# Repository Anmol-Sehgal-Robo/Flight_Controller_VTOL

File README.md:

# VTOL R2 Flight Controller

A single-string flight controller board for a 1.6 m tilt-rotor tricopter VTOL, designed in KiCad 9 and intended to run ArduPilot.

> **Status: design stage, not yet fabricated or bench-tested.** Items marked "simulated" or "assumed" have not been verified on hardware. Do not treat this design as flight-proven.

## Overview

- **Vehicle:** Heewing T1-style tilt-rotor tricopter, 1.6 m span, ~30 min flight time target
- **Firmware target:** ArduPilot
- **Architecture:** single-string (no redundancy)
- **Battery:** 6S Li-ion (6S2P 21700)

## Board

| Item | Value |
|---|---|
| MCU | STM32H743 |
| IMU | BMI270 |
| Barometer | BMP581 |
| Power stage | LT8641 buck, 2 MHz, 5 V rail |
| Size / layers | 70 x 55 mm, 4-layer |
| Servo outputs | 12 x 3-pin headers |
| Other | microSD, USB, SWD, buzzer |
| Fabrication | JLCPCB |

## Current state

- Layout: 0 unrouted nets, 0 DRC errors
- BOM checked against LCSC/JLC part pages
- Power stage simulated in LTspice and ngspice (efficiency figures indicative only, some derating values assumed)
- Not yet fabricated

## Safety

Unvalidated prototype. Do not fly until the board has passed bring-up and bench testing, and always power up first from a current-limited supply.

## License

To be decided.

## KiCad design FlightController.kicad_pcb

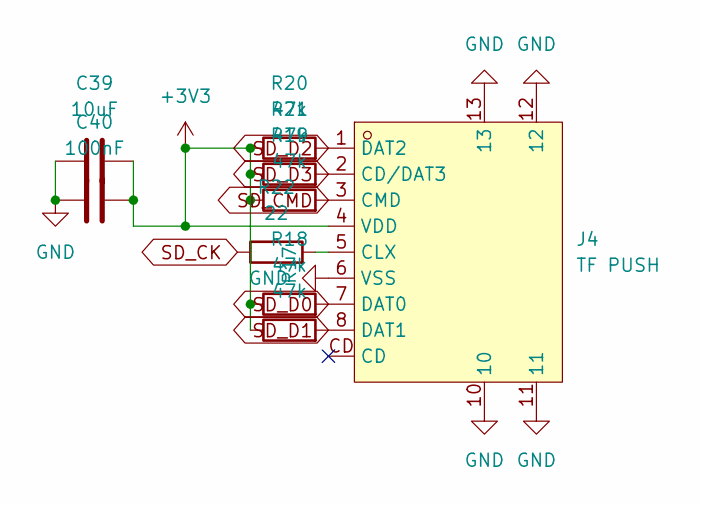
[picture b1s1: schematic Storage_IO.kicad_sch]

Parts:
C39: 10uF; C_0805_2012Metric; LCSC C15850
C40: 100nF; C_0603_1608Metric; LCSC C14663
J4: TF PUSH; TF-SMD_TF-PUSH; MPN TF PUSH; LCSC Part C393941
R17, R18, R19, R20, R21: 47k; R_0603_1608Metric; LCSC C25819
R22: 22; R_0603_1608Metric; LCSC C23345

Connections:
+3V3: C39.2, C40.2, J4.4 (VDD), R17.1, R18.1, R19.1, R20.1, R21.1; also elsewhere on the board
GND: C39.1, C40.1, J4.6 (VSS), J4.10, J4.11, J4.12, J4.13; also elsewhere on the board
unnamed: J4.5 (CLX), R22.2
SD_CK: R22.1; also elsewhere on the board
SD_CMD: J4.3 (CMD), R19.2; also elsewhere on the board
SD_D0: J4.7 (DAT0), R18.2; also elsewhere on the board
SD_D1: J4.8 (DAT1), R17.2; also elsewhere on the board
SD_D2: J4.1 (DAT2), R20.2; also elsewhere on the board
SD_D3: J4.2 (CD/DAT3), R21.2; also elsewhere on the board

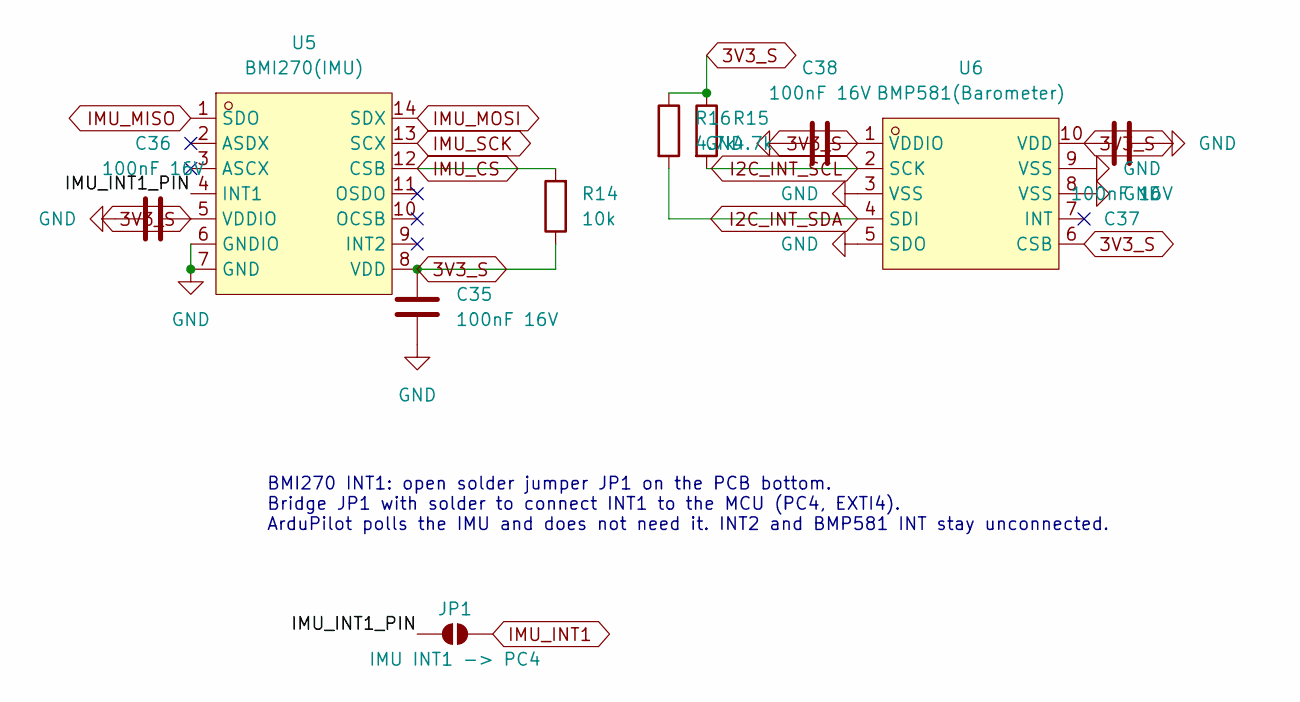
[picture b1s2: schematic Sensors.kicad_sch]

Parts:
C35, C36, C37, C38: 100nF 16V; C_0603_1608Metric; LCSC C14663
JP1: IMU INT1 -> PC4; SolderJumper-2_P1.3mm_Open_RoundedPad1.0x1.5mm
R14: 10k; R_0603_1608Metric; LCSC C25804
R15, R16: 4.7k; R_0603_1608Metric; LCSC C23162
U5: BMI270(IMU); LGA-14_L3.0-W2.5-P0.50-BR; MPN BMI270; LCSC Part C2836813
U6: BMP581(Barometer); LGA-10_L2.0-W2.0-P0.50-TL_BMP581; MPN BMP581; LCSC Part C5362283

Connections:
3V3_S: C35.1, C36.2, C37.2, C38.2, R14.1, R15.1, R16.1, U5.5 (VDDIO), U5.8 (VDD), U6.1 (VDDIO), U6.6 (CSB), U6.10 (VDD); also elsewhere on the board
/Sensors/IMU_INT1_PIN: JP1.1 (A), U5.4 (INT1)
GND: C35.2, C36.1, C37.1, C38.1, U5.6 (GNDIO), U5.7 (GND), U6.3 (VSS), U6.5 (SDO), U6.8 (VSS), U6.9 (VSS); also elsewhere on the board
I2C_INT_SCL: R15.2, U6.2 (SCK); also elsewhere on the board
I2C_INT_SDA: R16.2, U6.4 (SDI); also elsewhere on the board
IMU_CS: R14.2, U5.12 (CSB); also elsewhere on the board
IMU_INT1: JP1.2 (B); also elsewhere on the board
IMU_MISO: U5.1 (SDO); also elsewhere on the board
IMU_MOSI: U5.14 (SDX); also elsewhere on the board
IMU_SCK: U5.13 (SCX); also elsewhere on the board

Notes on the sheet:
BMI270 INT1: open solder jumper JP1 on the PCB bottom. Bridge JP1 with solder to connect INT1 to the MCU (PC4, EXTI4). ArduPilot polls the IMU and does not need it. INT2 and BMP581 INT stay unconnected.

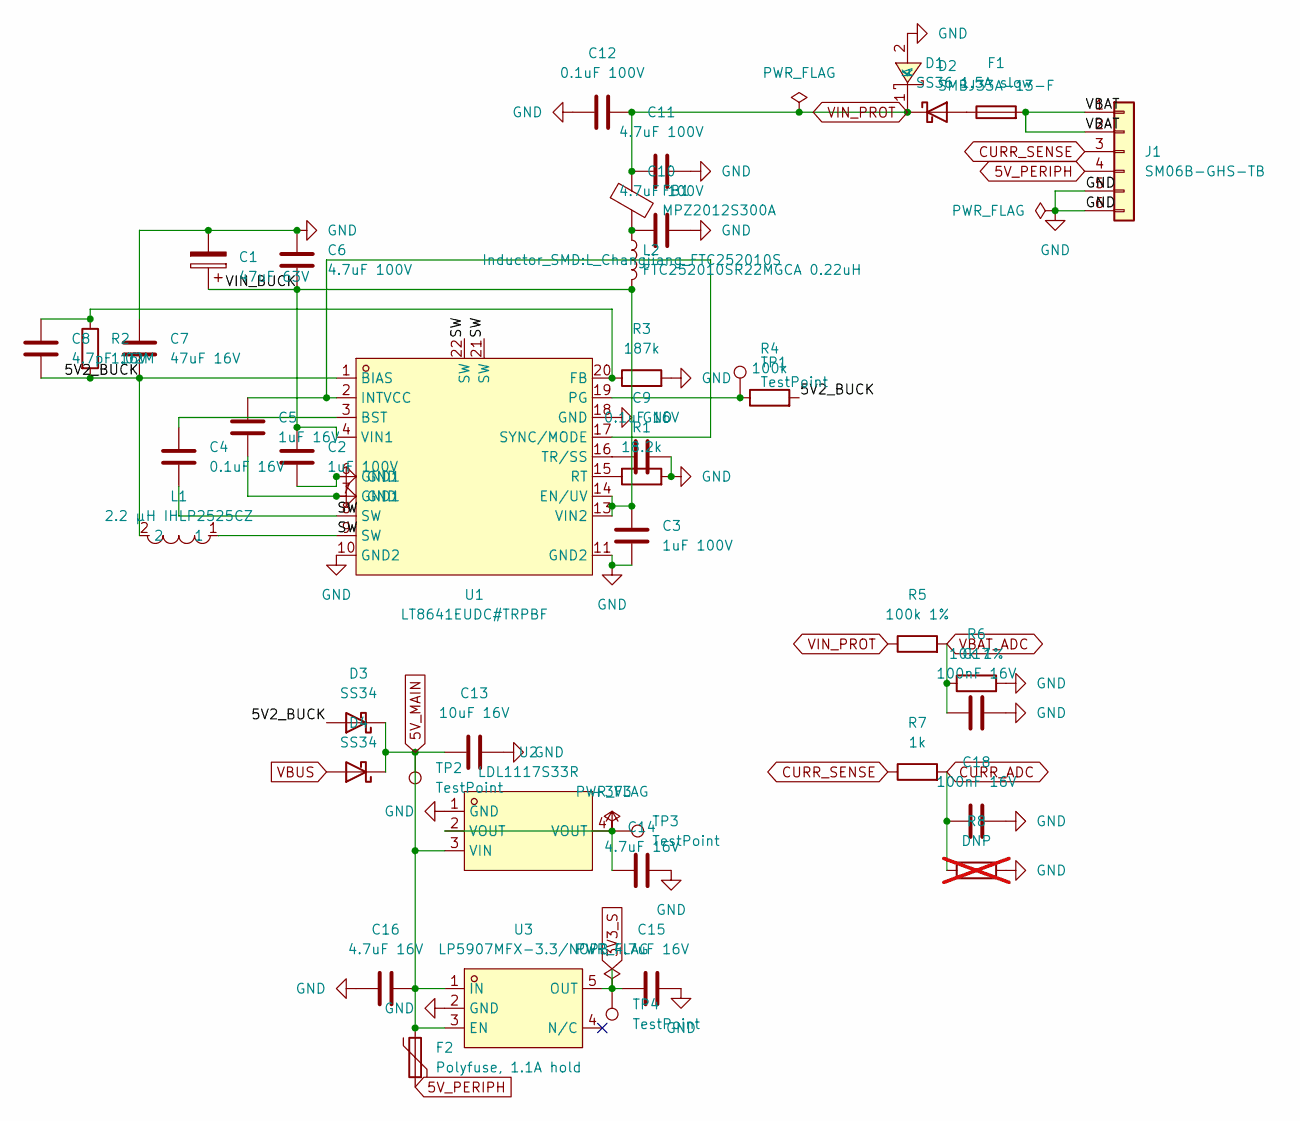
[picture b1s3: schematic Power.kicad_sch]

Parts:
C1: 47uF 63V; CP_Elec_8x10; LCSC C278401
C2, C3: 1uF 100V; C_0805_2012Metric; LCSC C5370002
C4, C9: 0.1uF 16V; C_0603_1608Metric; LCSC C14663
C5: 1uF 16V; C_0603_1608Metric; LCSC C15849
C6, C10, C11: 4.7uF 100V; C_1210_3225Metric; LCSC C49451356
C7: 47uF 16V; C_1210_3225Metric; LCSC C77101
C8: 4.7pF 16V; C_0603_1608Metric; LCSC C1669
C12: 0.1uF 100V; C_0603_1608Metric; LCSC C696916
C13: 10uF 16V; C_0805_2012Metric; LCSC C15850
C14: 4.7uF 16V; C_0805_2012Metric; LCSC C1779
C15, C16: 4.7uF 16V; C_0603_1608Metric; LCSC C19666
C17, C18: 100nF 16V; C_0603_1608Metric; LCSC C14663
D1: SS36; D_SMB; LCSC C35490
D2: SMBJ33A-13-F; SMB_L4.6-W3.6-LS5.3-RD; MPN SMBJ33A-13-F; LCSC Part C135067
D3, D4: SS34; D_SMA; LCSC C8678
F1: 1.5A slow; Fuse_1206_3216Metric; LCSC C151143
F2: Polyfuse, 1.1A hold; Fuse_1206_3216Metric; LCSC C269119
FB1: MPZ2012S300A; L_0805_2012Metric; LCSC C136227
J1: SM06B-GHS-TB; JST_GH_SM06B-GHS-TB_1x06-1MP_P1.25mm_Horizontal; LCSC C133065
L1: 2.2 µH IHLP2525CZ; IND-SMD_L6.5-W6.5_IHLP-2525; MPN IHLP2525CZER2R2M01; LCSC Part C540967
L2: FTC252010SR22MGCA 0.22uH; L_Changjiang_FTC252010S; LCSC C48888294
R1: 18.2k; R_0603_1608Metric; LCSC C22892
R2: 1.02M; R_0603_1608Metric; LCSC C5713277
R3: 187k; R_0603_1608Metric; LCSC C22896
R4: 100k; R_0603_1608Metric; LCSC C25803
R5: 100k 1%; R_0603_1608Metric; LCSC C25803
R6: 10k 1%; R_0603_1608Metric; LCSC C25804
R7: 1k; R_0603_1608Metric; LCSC C21190
R8: DNP; R_0603_1608Metric; not fitted
TP1, TP2, TP3, TP4: TestPoint; TestPoint_Pad_D1.0mm
U1: LT8641EUDC#TRPBF; QFN-20_L4.0-W3.0-P0.50-TL_LT8641EUDC; MPN LT8641EUDC#TRPBF; LCSC Part C462660
U2: LDL1117S33R; SOT-223-4_L6.5-W3.5-P2.30-LS7.0-BR; MPN LDL1117S33R; LCSC Part C435835
U3: LP5907MFX-3.3/NOPB; SOT-23-5_L3.0-W1.7-P0.95-LS2.8-BR; MPN LP5907MFX-3.3/NOPB; LCSC Part C80670

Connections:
3V3_S: C15.1, TP4.1, U3.5 (OUT); also elsewhere on the board
5V_MAIN: C13.1, C16.2, D3.1 (K), D4.1 (K), F2.2, TP2.1, U2.3 (VIN), U3.1 (IN), U3.3 (EN); also elsewhere on the board
5V_PERIPH: F2.1, J1.4; also elsewhere on the board
+3V3: C14.1, TP3.1, U2.2 (VOUT), U2.4 (VOUT); also elsewhere on the board
/Power/5V2_BUCK: C7.2, C8.2, D3.2 (A), L1.2, R2.2, R4.2, U1.1 (BIAS)
/Power/SW: C4.2, L1.1, U1.8 (SW), U1.9 (SW), U1.21 (SW), U1.22 (SW)
/Power/VBAT: F1.2, J1.1, J1.2
/Power/VIN_BUCK: C1.1, C2.1, C3.1, C6.2, L2.2, U1.4 (VIN1), U1.13 (VIN2), U1.14 (EN/UV)
CURR_ADC: C18.1, R7.2, R8.1; also elsewhere on the board
CURR_SENSE: J1.3, R7.1
GND: C1.2, C2.2, C3.2, C5.2, C6.1, C7.1, C9.2, C10.2, C11.2, C12.1, C13.2, C14.2, C15.2, C16.1, C17.2, C18.2, D2.2 (A), J1.5, J1.6, R1.2, R3.2, R6.2, R8.2, U1.6 (GND1), U1.7 (GND1), U1.10 (GND2), U1.11 (GND2), U1.18 (GND), U2.1 (GND), U3.2 (GND); also elsewhere on the board
unnamed: C10.1, FB1.2, L2.1
unnamed: D1.2 (A), F1.1
unnamed: C4.1, U1.3 (BST)
unnamed: C8.1, R2.1, R3.1, U1.20 (FB)
unnamed: C5.1, U1.2 (INTVCC), U1.17 (SYNC/MODE)
unnamed: R4.1, TP1.1, U1.19 (PG)
unnamed: R1.1, U1.15 (RT)
unnamed: C9.1, U1.16 (TR/SS)
VBAT_ADC: C17.1, R5.2, R6.1; also elsewhere on the board
VBUS: D4.2 (A); also elsewhere on the board
VIN_PROT: C11.1, C12.2, D1.1 (K), D2.1 (K), FB1.1, R5.1

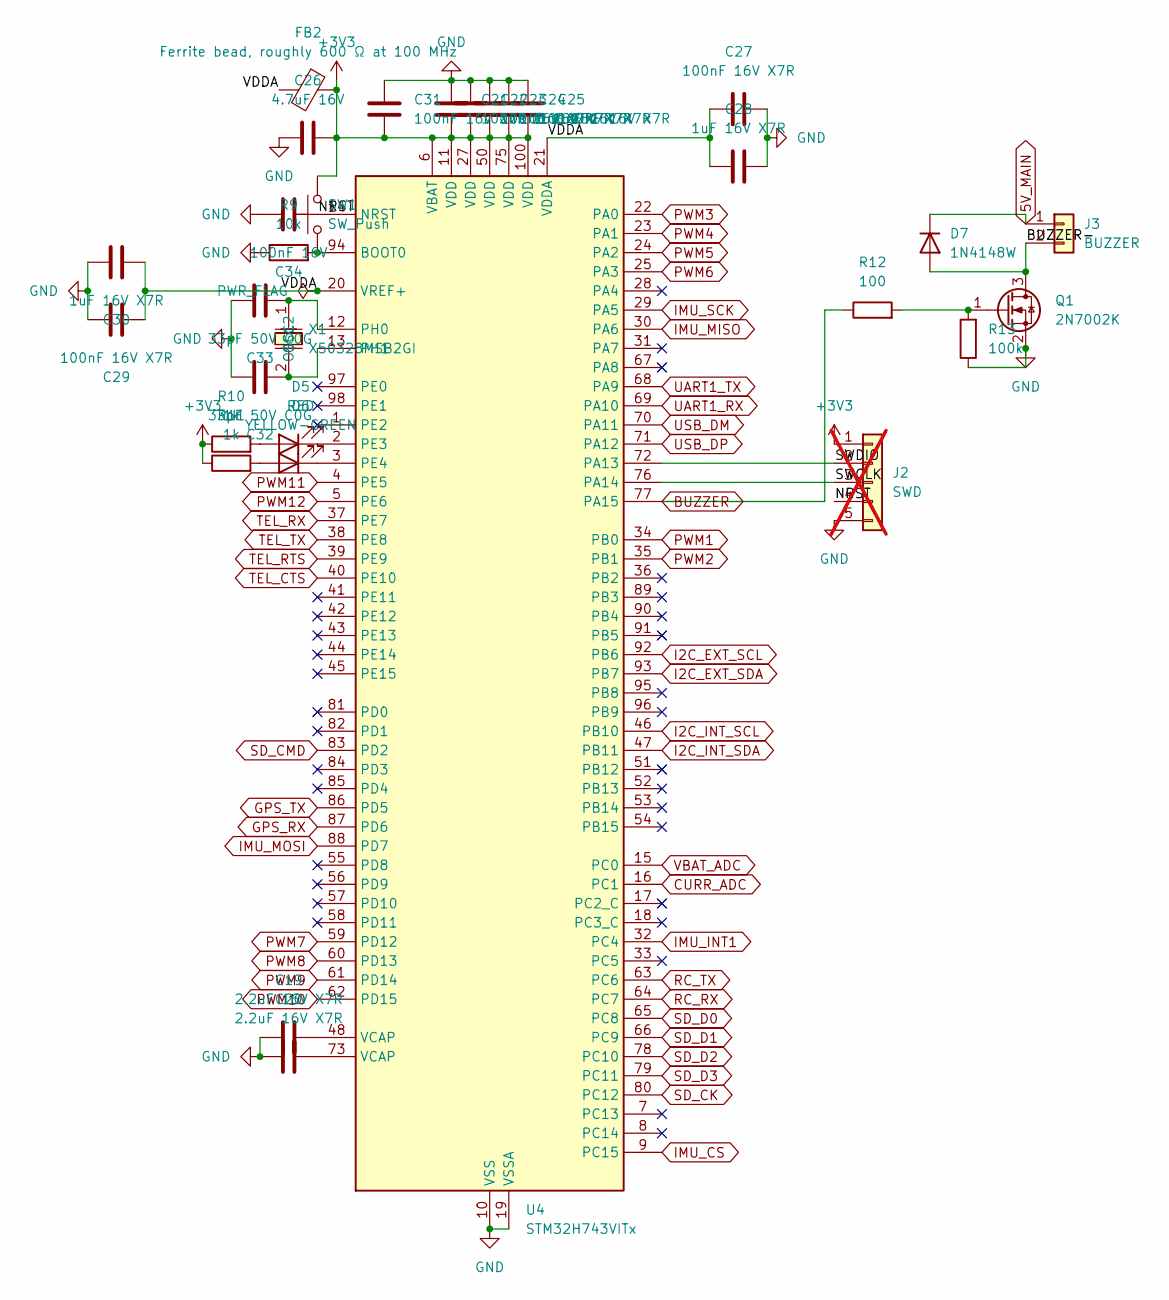
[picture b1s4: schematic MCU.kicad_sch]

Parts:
C19, C20: 2.2uF 16V X7R; C_0603_1608Metric; LCSC C914769
C21, C22, C23, C24, C25, C27, C29, C31: 100nF 16V X7R; C_0603_1608Metric; LCSC C14663
C26: 4.7uF 16V; C_0805_2012Metric; LCSC C1779
C28, C30: 1uF 16V X7R; C_0603_1608Metric; LCSC C106248
C32, C33: 33pF 50V C0G; C_0603_1608Metric; LCSC C1663
C34: 100nF 16V; C_0603_1608Metric; LCSC C14663
D5: RED; LED_0603_1608Metric; LCSC C2286
D6: YELLOW-GREEN; LED_0603_1608Metric; LCSC C84264
D7: 1N4148W; D_SOD-123; LCSC C81598
FB2: Ferrite bead, roughly 600 Ω at 100 MHz; L_0603_1608Metric; LCSC C1002
J2: SWD; PinHeader_1x05_P1.27mm_Vertical; not fitted
J3: BUZZER; JST_GH_SM02B-GHS-TB_1x02-1MP_P1.25mm_Horizontal; LCSC C189893
Q1: 2N7002K; SOT-23; LCSC C414015
R9: 10k; R_0603_1608Metric; LCSC C25804
R10, R11: 1k; R_0603_1608Metric; LCSC C21190
R12: 100; R_0603_1608Metric; LCSC C22775
R13: 100k; R_0603_1608Metric; LCSC C25803
SW1: SW_Push; SW_SPST_TS-1088-xR020; LCSC C720477
U4: STM32H743VITx; LQFP-100_14x14mm_P0.5mm; LCSC C114409
X1: X50328MSB2GI; CRYSTAL-SMD_L5.0-W3.2; MPN X50328MSB2GI; LCSC Part C115962

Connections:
5V_MAIN: D7.1 (K), J3.1; also elsewhere on the board
+3V3: C21.2, C22.2, C23.2, C24.2, C25.2, C26.1, C31.2, FB2.1, J2.1, R10.1, R11.1, SW1.2, U4.6 (VBAT), U4.11 (VDD), U4.27 (VDD), U4.50 (VDD), U4.75 (VDD), U4.100 (VDD); also elsewhere on the board
/MCU/BUZZER-: D7.2 (A), J3.2, Q1.3 (D)
/MCU/NRST: C34.1, J2.4, U4.14 (NRST)
/MCU/SWCLK: J2.3, U4.76 (PA14)
/MCU/SWDIO: J2.2, U4.72 (PA13)
/MCU/VDDA: C27.1, C28.1, C29.1, C30.1, FB2.2, U4.20 (VREF+), U4.21 (VDDA)
BUZZER: R12.1, U4.77 (PA15)
CURR_ADC: U4.16 (PC1); also elsewhere on the board
GND: C19.1, C20.1, C21.1, C22.1, C23.1, C24.1, C25.1, C26.2, C27.2, C28.2, C29.2, C30.2, C31.1, C32.2, C33.2, C34.2, J2.5, Q1.2 (S), R9.1, R13.1, U4.10 (VSS), U4.19 (VSSA), U4.26 (VSS), U4.49 (VSS), U4.74 (VSS), U4.99 (VSS); also elsewhere on the board
GPS_RX: U4.87 (PD6); also elsewhere on the board
GPS_TX: U4.86 (PD5); also elsewhere on the board
I2C_EXT_SCL: U4.92 (PB6); also elsewhere on the board
I2C_EXT_SDA: U4.93 (PB7); also elsewhere on the board
I2C_INT_SCL: U4.46 (PB10); also elsewhere on the board
I2C_INT_SDA: U4.47 (PB11); also elsewhere on the board
IMU_CS: U4.9 (PC15); also elsewhere on the board
IMU_INT1: U4.32 (PC4); also elsewhere on the board
IMU_MISO: U4.30 (PA6); also elsewhere on the board
IMU_MOSI: U4.88 (PD7); also elsewhere on the board
IMU_SCK: U4.29 (PA5); also elsewhere on the board
unnamed: C19.2, U4.48 (VCAP)
unnamed: C20.2, U4.73 (VCAP)
unnamed: D5.2 (A), R10.2
unnamed: D5.1 (K), U4.2 (PE3)
unnamed: D6.2 (A), R11.2
unnamed: D6.1 (K), U4.3 (PE4)
unnamed: Q1.1 (G), R12.2, R13.2
unnamed: R9.2, SW1.1, U4.94 (BOOT0)
unnamed: C33.1, U4.12 (PH0), X1.1 (OSC1)
unnamed: C32.1, U4.13 (PH1), X1.2 (OSC2)
PWM1: U4.34 (PB0); also elsewhere on the board
PWM2: U4.35 (PB1); also elsewhere on the board
PWM3: U4.22 (PA0); also elsewhere on the board
PWM4: U4.23 (PA1); also elsewhere on the board
PWM5: U4.24 (PA2); also elsewhere on the board
PWM6: U4.25 (PA3); also elsewhere on the board
PWM7: U4.59 (PD12); also elsewhere on the board
PWM8: U4.60 (PD13); also elsewhere on the board
PWM9: U4.61 (PD14); also elsewhere on the board
PWM10: U4.62 (PD15); also elsewhere on the board
PWM11: U4.4 (PE5); also elsewhere on the board
PWM12: U4.5 (PE6); also elsewhere on the board
RC_RX: U4.64 (PC7); also elsewhere on the board
RC_TX: U4.63 (PC6); also elsewhere on the board
SD_CK: U4.80 (PC12); also elsewhere on the board
SD_CMD: U4.83 (PD2); also elsewhere on the board
SD_D0: U4.65 (PC8); also elsewhere on the board
SD_D1: U4.66 (PC9); also elsewhere on the board
SD_D2: U4.78 (PC10); also elsewhere on the board
SD_D3: U4.79 (PC11); also elsewhere on the board
TEL_CTS: U4.40 (PE10); also elsewhere on the board
TEL_RTS: U4.39 (PE9); also elsewhere on the board
TEL_RX: U4.37 (PE7); also elsewhere on the board
TEL_TX: U4.38 (PE8); also elsewhere on the board
UART1_RX: U4.69 (PA10); also elsewhere on the board
UART1_TX: U4.68 (PA9); also elsewhere on the board
USB_DM: U4.70 (PA11); also elsewhere on the board
USB_DP: U4.71 (PA12); also elsewhere on the board
VBAT_ADC: U4.15 (PC0); also elsewhere on the board

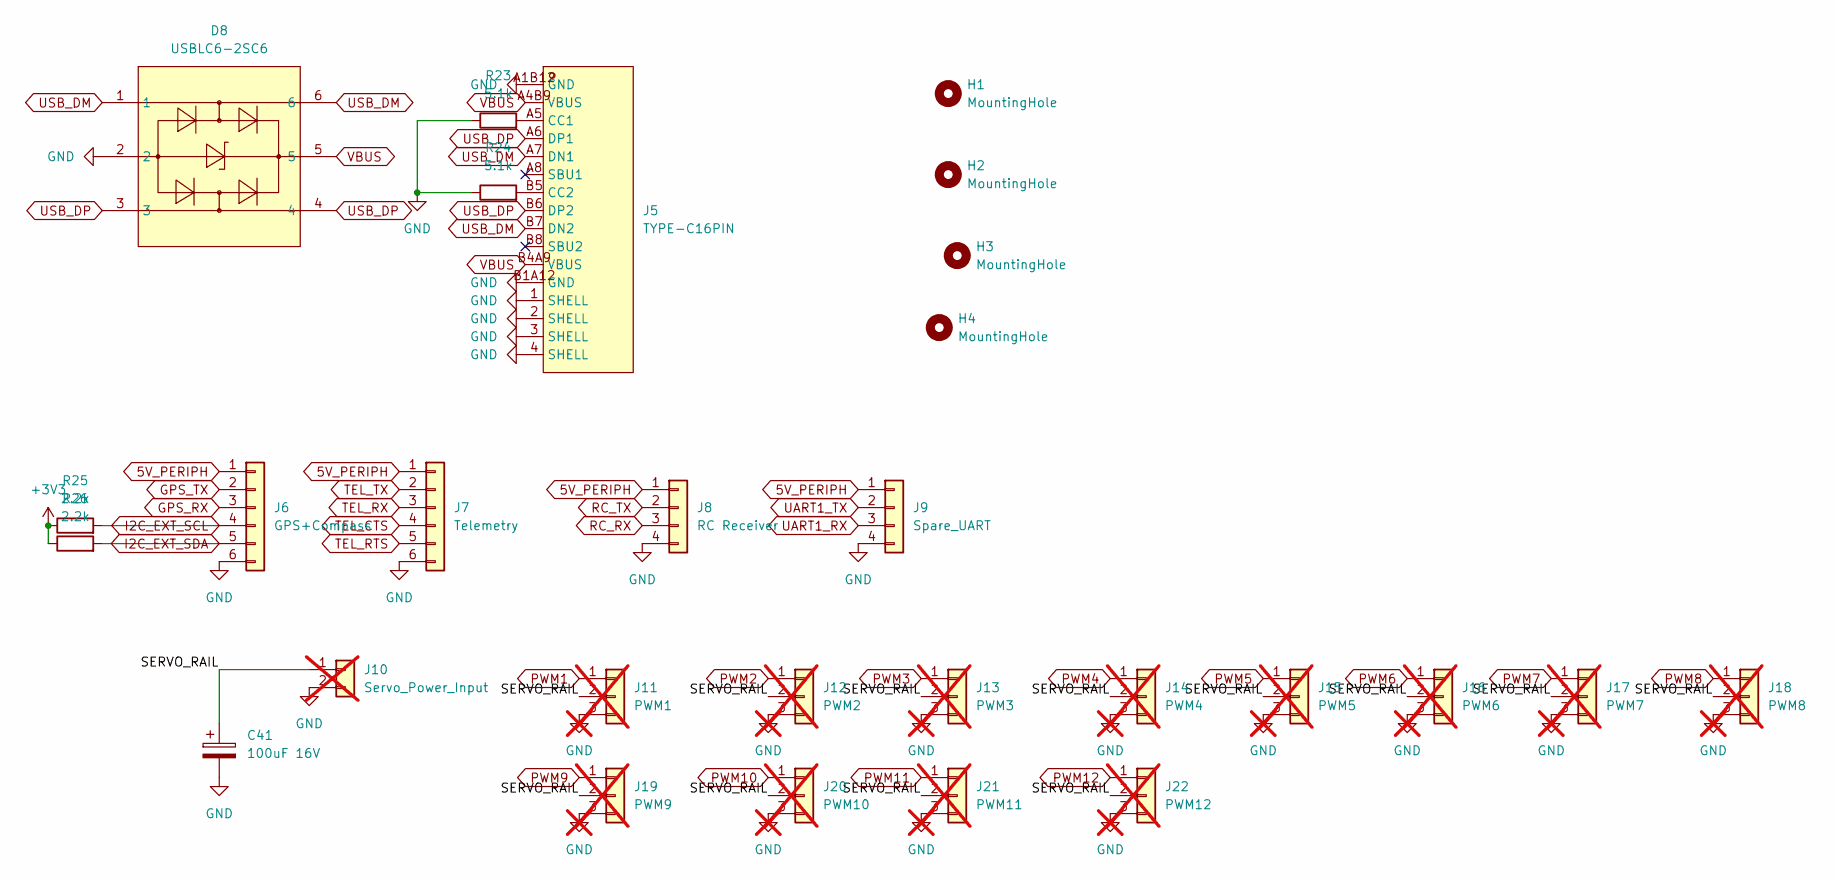
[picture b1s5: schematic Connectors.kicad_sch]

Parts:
C41: 100uF 16V; CP_Elec_6.3x7.7; LCSC C72476
D8: USBLC6-2SC6; SOT-23-6_L2.9-W1.6-P0.95-LS2.8-BL; MPN USBLC6-2SC6; LCSC Part C7519
H1, H2, H3, H4: MountingHole; MountingHole_3.2mm_M3
J5: TYPE-C16PIN; USB-C-SMD_TYPE-C16PIN; MPN TYPE-C16PIN; LCSC Part C393939
J6: GPS+Compass; JST_GH_SM06B-GHS-TB_1x06-1MP_P1.25mm_Horizontal; LCSC C133065
J7: Telemetry; JST_GH_SM06B-GHS-TB_1x06-1MP_P1.25mm_Horizontal; LCSC C133065
J8: RC Receiver; JST_GH_SM04B-GHS-TB_1x04-1MP_P1.25mm_Horizontal; LCSC C189895
J9: Spare_UART; JST_GH_SM04B-GHS-TB_1x04-1MP_P1.25mm_Horizontal; LCSC C189895
J10: Servo_Power_Input; PinHeader_1x02_P2.54mm_Vertical; not fitted
J11: PWM1; PinHeader_1x03_P2.54mm_Vertical; not fitted
J12: PWM2; PinHeader_1x03_P2.54mm_Vertical; not fitted
J13: PWM3; PinHeader_1x03_P2.54mm_Vertical; not fitted
J14: PWM4; PinHeader_1x03_P2.54mm_Vertical; not fitted
J15: PWM5; PinHeader_1x03_P2.54mm_Vertical; not fitted
J16: PWM6; PinHeader_1x03_P2.54mm_Vertical; not fitted
J17: PWM7; PinHeader_1x03_P2.54mm_Vertical; not fitted
J18: PWM8; PinHeader_1x03_P2.54mm_Vertical; not fitted
J19: PWM9; PinHeader_1x03_P2.54mm_Vertical; not fitted
J20: PWM10; PinHeader_1x03_P2.54mm_Vertical; not fitted
J21: PWM11; PinHeader_1x03_P2.54mm_Vertical; not fitted
J22: PWM12; PinHeader_1x03_P2.54mm_Vertical; not fitted
R23, R24: 5.1k; R_0603_1608Metric; LCSC C23186
R25, R26: 2.2k; R_0603_1608Metric; LCSC C4190

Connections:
5V_PERIPH: J6.1, J7.1, J8.1, J9.1; also elsewhere on the board
+3V3: R25.1, R26.1; also elsewhere on the board
/Connectors/SERVO_RAIL: C41.1, J10.1, J11.2, J12.2, J13.2, J14.2, J15.2, J16.2, J17.2, J18.2, J19.2, J20.2, J21.2, J22.2
GND: C41.2, D8.2, J5.1 (SHELL), J5.2 (SHELL), J5.3 (SHELL), J5.4 (SHELL), J5.A1B12 (GND), J5.B1A12 (GND), J6.6, J7.6, J8.4, J9.4, J10.2, J11.3, J12.3, J13.3, J14.3, J15.3, J16.3, J17.3, J18.3, J19.3, J20.3, J21.3, J22.3, R23.1, R24.1; also elsewhere on the board
GPS_RX: J6.3; also elsewhere on the board
GPS_TX: J6.2; also elsewhere on the board
I2C_EXT_SCL: J6.4, R25.2; also elsewhere on the board
I2C_EXT_SDA: J6.5, R26.2; also elsewhere on the board
unnamed: J5.A5 (CC1), R23.2
unnamed: J5.B5 (CC2), R24.2
PWM1: J11.1; also elsewhere on the board
PWM2: J12.1; also elsewhere on the board
PWM3: J13.1; also elsewhere on the board
PWM4: J14.1; also elsewhere on the board
PWM5: J15.1; also elsewhere on the board
PWM6: J16.1; also elsewhere on the board
PWM7: J17.1; also elsewhere on the board
PWM8: J18.1; also elsewhere on the board
PWM9: J19.1; also elsewhere on the board
PWM10: J20.1; also elsewhere on the board
PWM11: J21.1; also elsewhere on the board
PWM12: J22.1; also elsewhere on the board
RC_RX: J8.3; also elsewhere on the board
RC_TX: J8.2; also elsewhere on the board
TEL_CTS: J7.4; also elsewhere on the board
TEL_RTS: J7.5; also elsewhere on the board
TEL_RX: J7.3; also elsewhere on the board
TEL_TX: J7.2; also elsewhere on the board
UART1_RX: J9.3; also elsewhere on the board
UART1_TX: J9.2; also elsewhere on the board
USB_DM: D8.1, D8.6, J5.A7 (DN1), J5.B7 (DN2); also elsewhere on the board
USB_DP: D8.3, D8.4, J5.A6 (DP1), J5.B6 (DP2); also elsewhere on the board
VBUS: D8.5, J5.A4B9 (VBUS), J5.B4A9 (VBUS); also elsewhere on the board

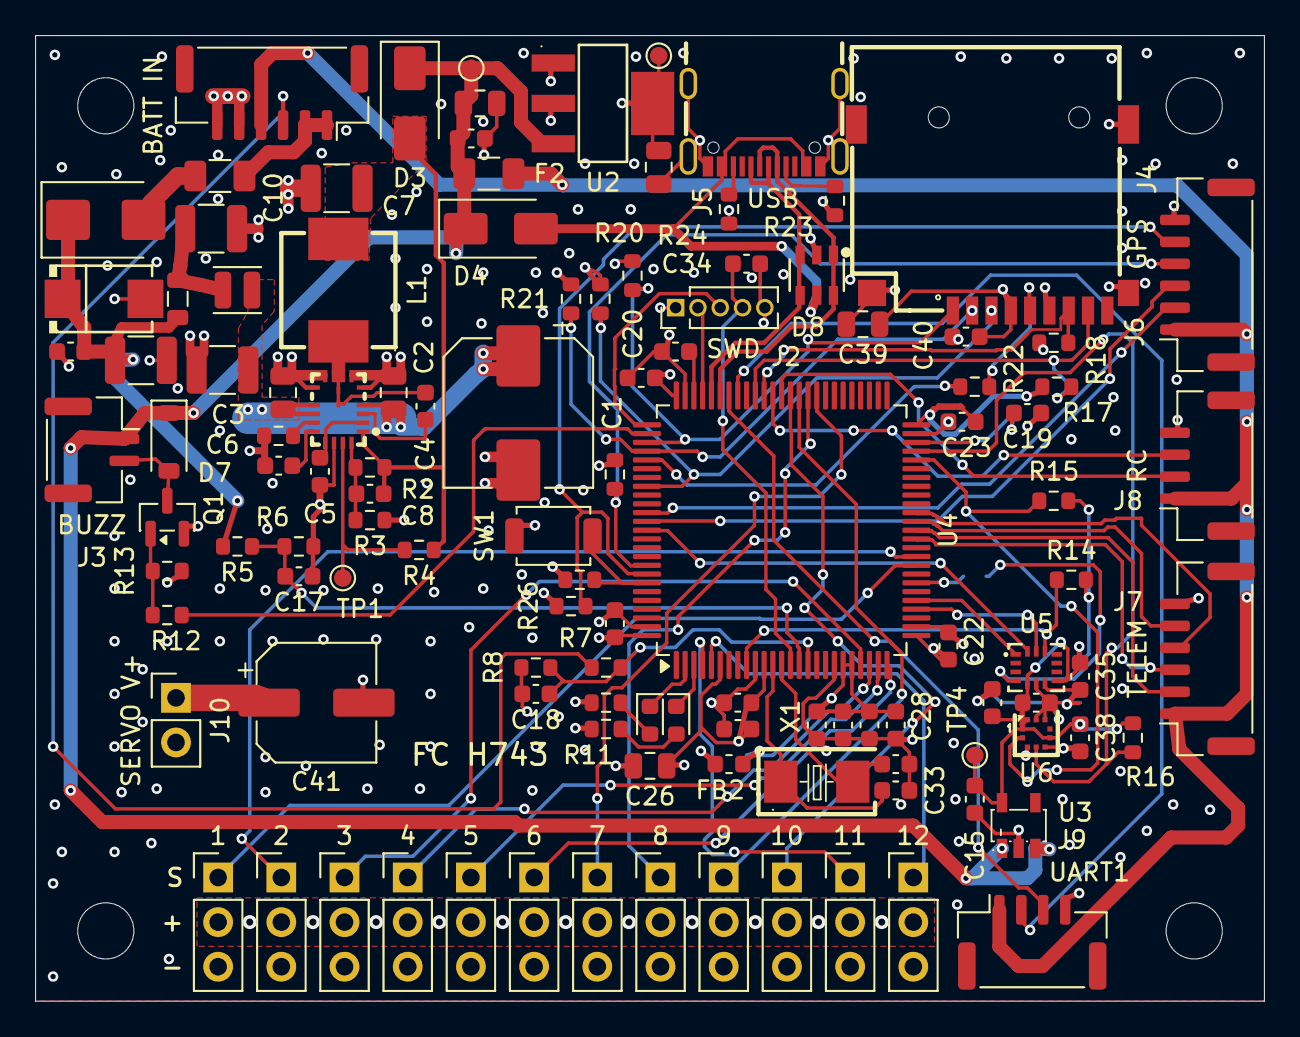
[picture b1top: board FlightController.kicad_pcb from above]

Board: 4 copper layers, 70.0 x 55.0 mm, 121 parts (1 on the bottom side), 82 nets.
